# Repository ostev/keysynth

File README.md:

# KeySynth

KeySynth is an equation synthesiser built around a traditional mechanical keyboard!

An equation synthesiser is a wavetable synthesiser that allows the user to input arbitrary mathematical expressions which can then be used to create sounds! It also features a basic low-pass filter, with more effects (hopefully) to come.

In addition, it can act as a regular computer keyboard.

This repository contains the open-source PCBs (missing non-open source components from UltraLibrarian and SnapMagic) as well as project's source code. The PCB contains an 80% keyboard, three knobs, a pinout for a display, an ESP32-S3 (used for audio, display and USB) and an RP2040 (used for interfacing with the keyboard matrix due to limited pin availability).

The source code is divided into the following crates:

- [`calc`](crates/calc/) for the tiny programming language used for synthesis,
- [`repl`](crates/repl/) for a simple REPL for `calc` which is used for debugging and implementing new langauge features,
- [`synth`](crates/synth/) for the audio engine,
- [`keyboard_protocol`](crates/keyboard_protocol/) for interfacing between the RP2040 and the ESP32-S3 about keyboards and two of the three knobs over UART serial,
- [`keyboard_rp2040`](crates/keyboard_rp2040/) for running the keyboard matrix on the RP2040, and
- [`app`](crates/app/) for running the main application on the ESP32-S3.

## Demo

There'll be a link to a video demo up on YouTube once I've filmed it.

## :construction: :construction: :construction: Roadmap

This project isn't finished! Equation synthesis and keyboard input all work, but I want to implement some more features before considering it complete:

- [ ] USB MIDI input from host
- [ ] Improve PCB layout (as-is there are a couple of design flaws that don't inhabit the current set of functionality but limit the utility of 3.5mm audio output. I'm not sure when I'll be able to fix this: it'll be when I've made enough changes that I can justify the cost of ordering another set of PCBs.)
- [ ] Add more audio effects, like reverb and chorus.
- [ ] Add more audio synthesis engines, like subtractive or FM synthesis.

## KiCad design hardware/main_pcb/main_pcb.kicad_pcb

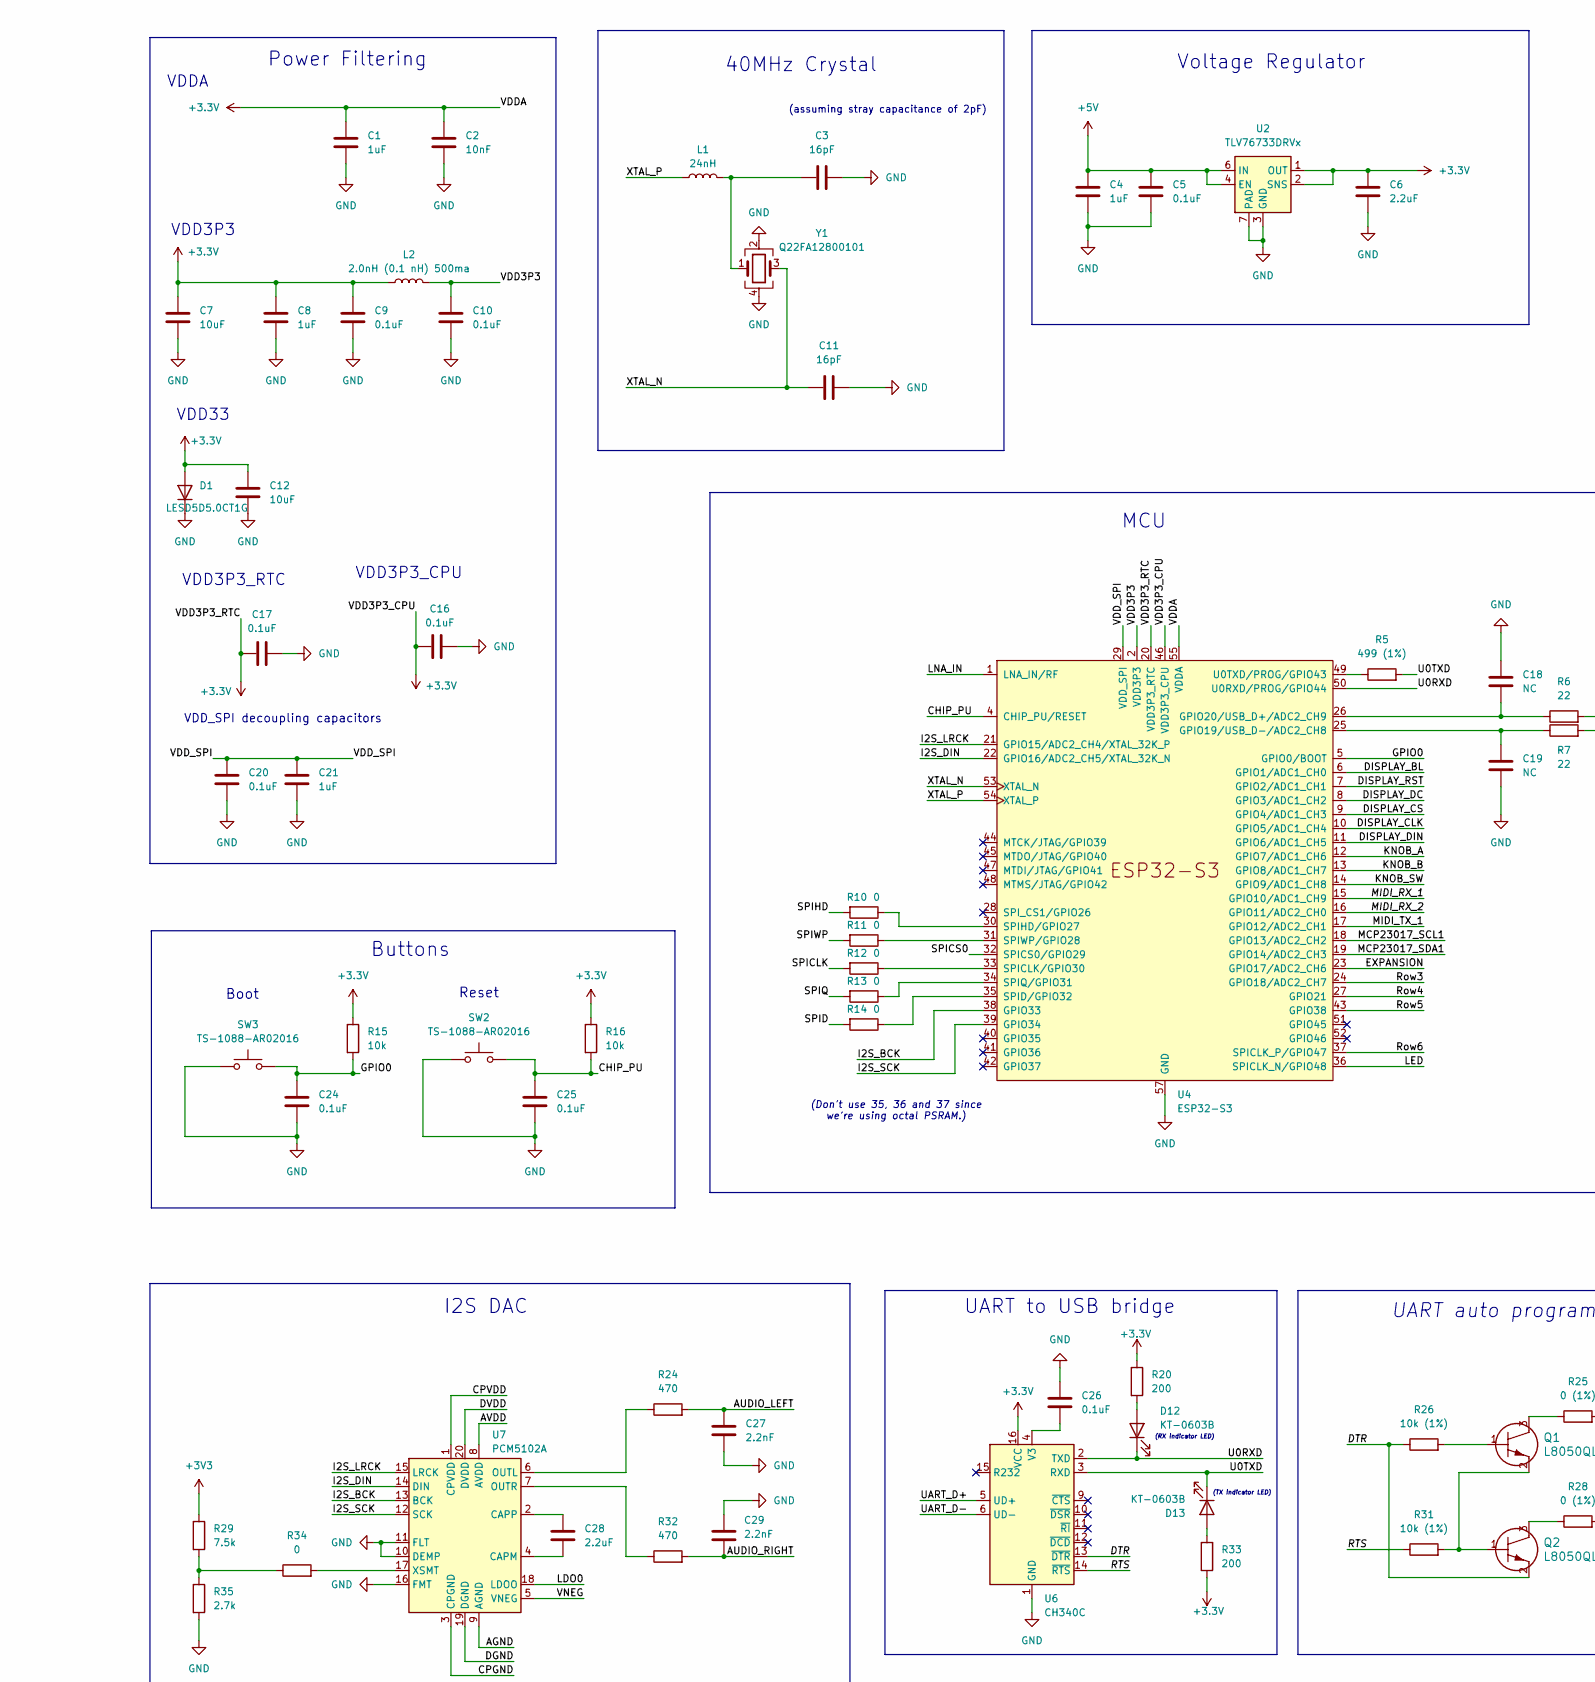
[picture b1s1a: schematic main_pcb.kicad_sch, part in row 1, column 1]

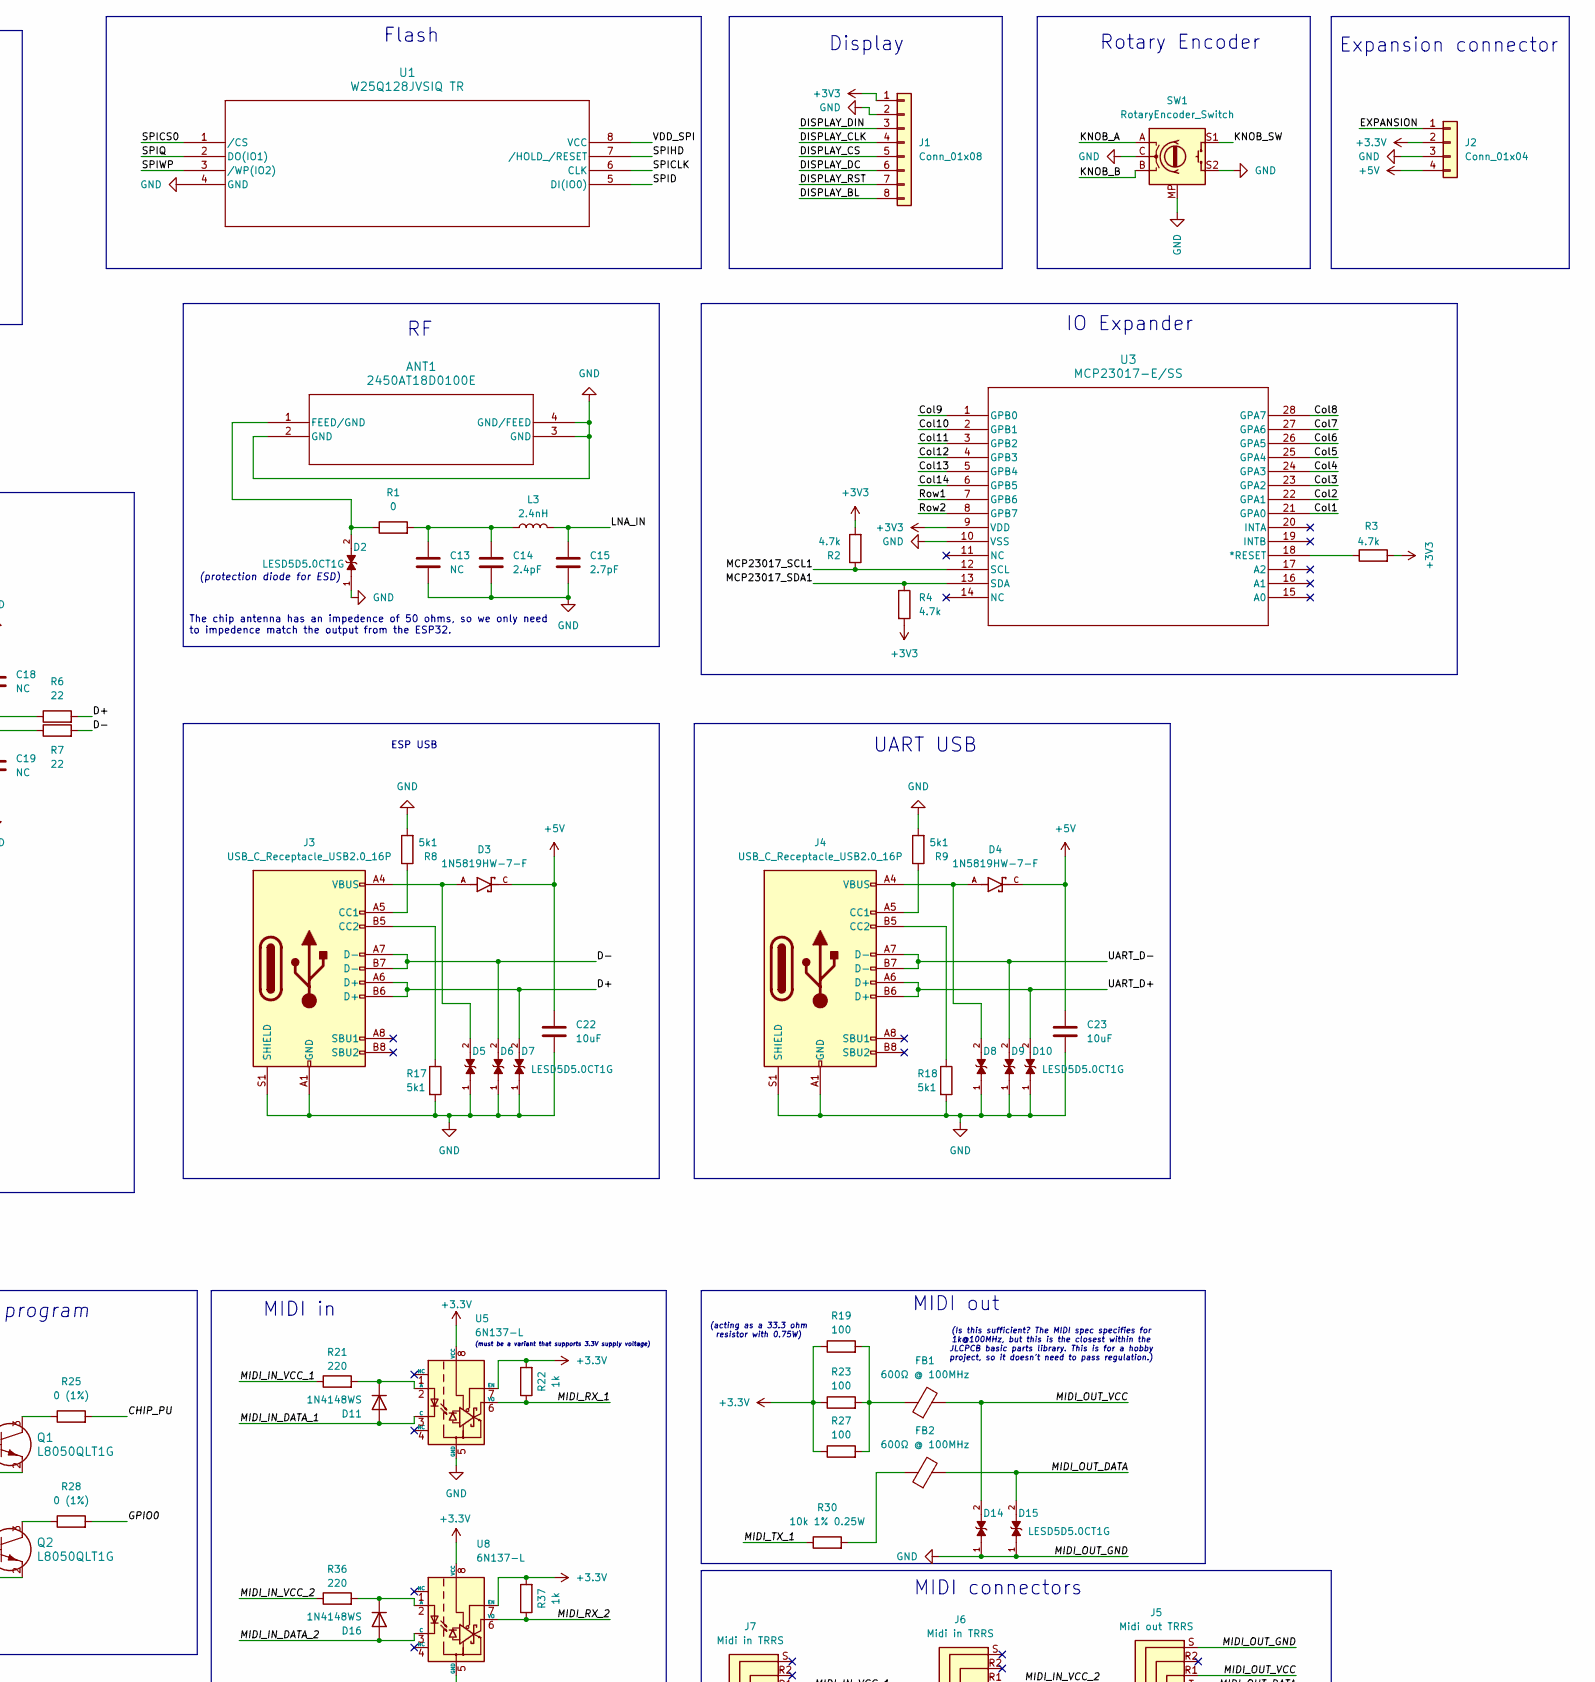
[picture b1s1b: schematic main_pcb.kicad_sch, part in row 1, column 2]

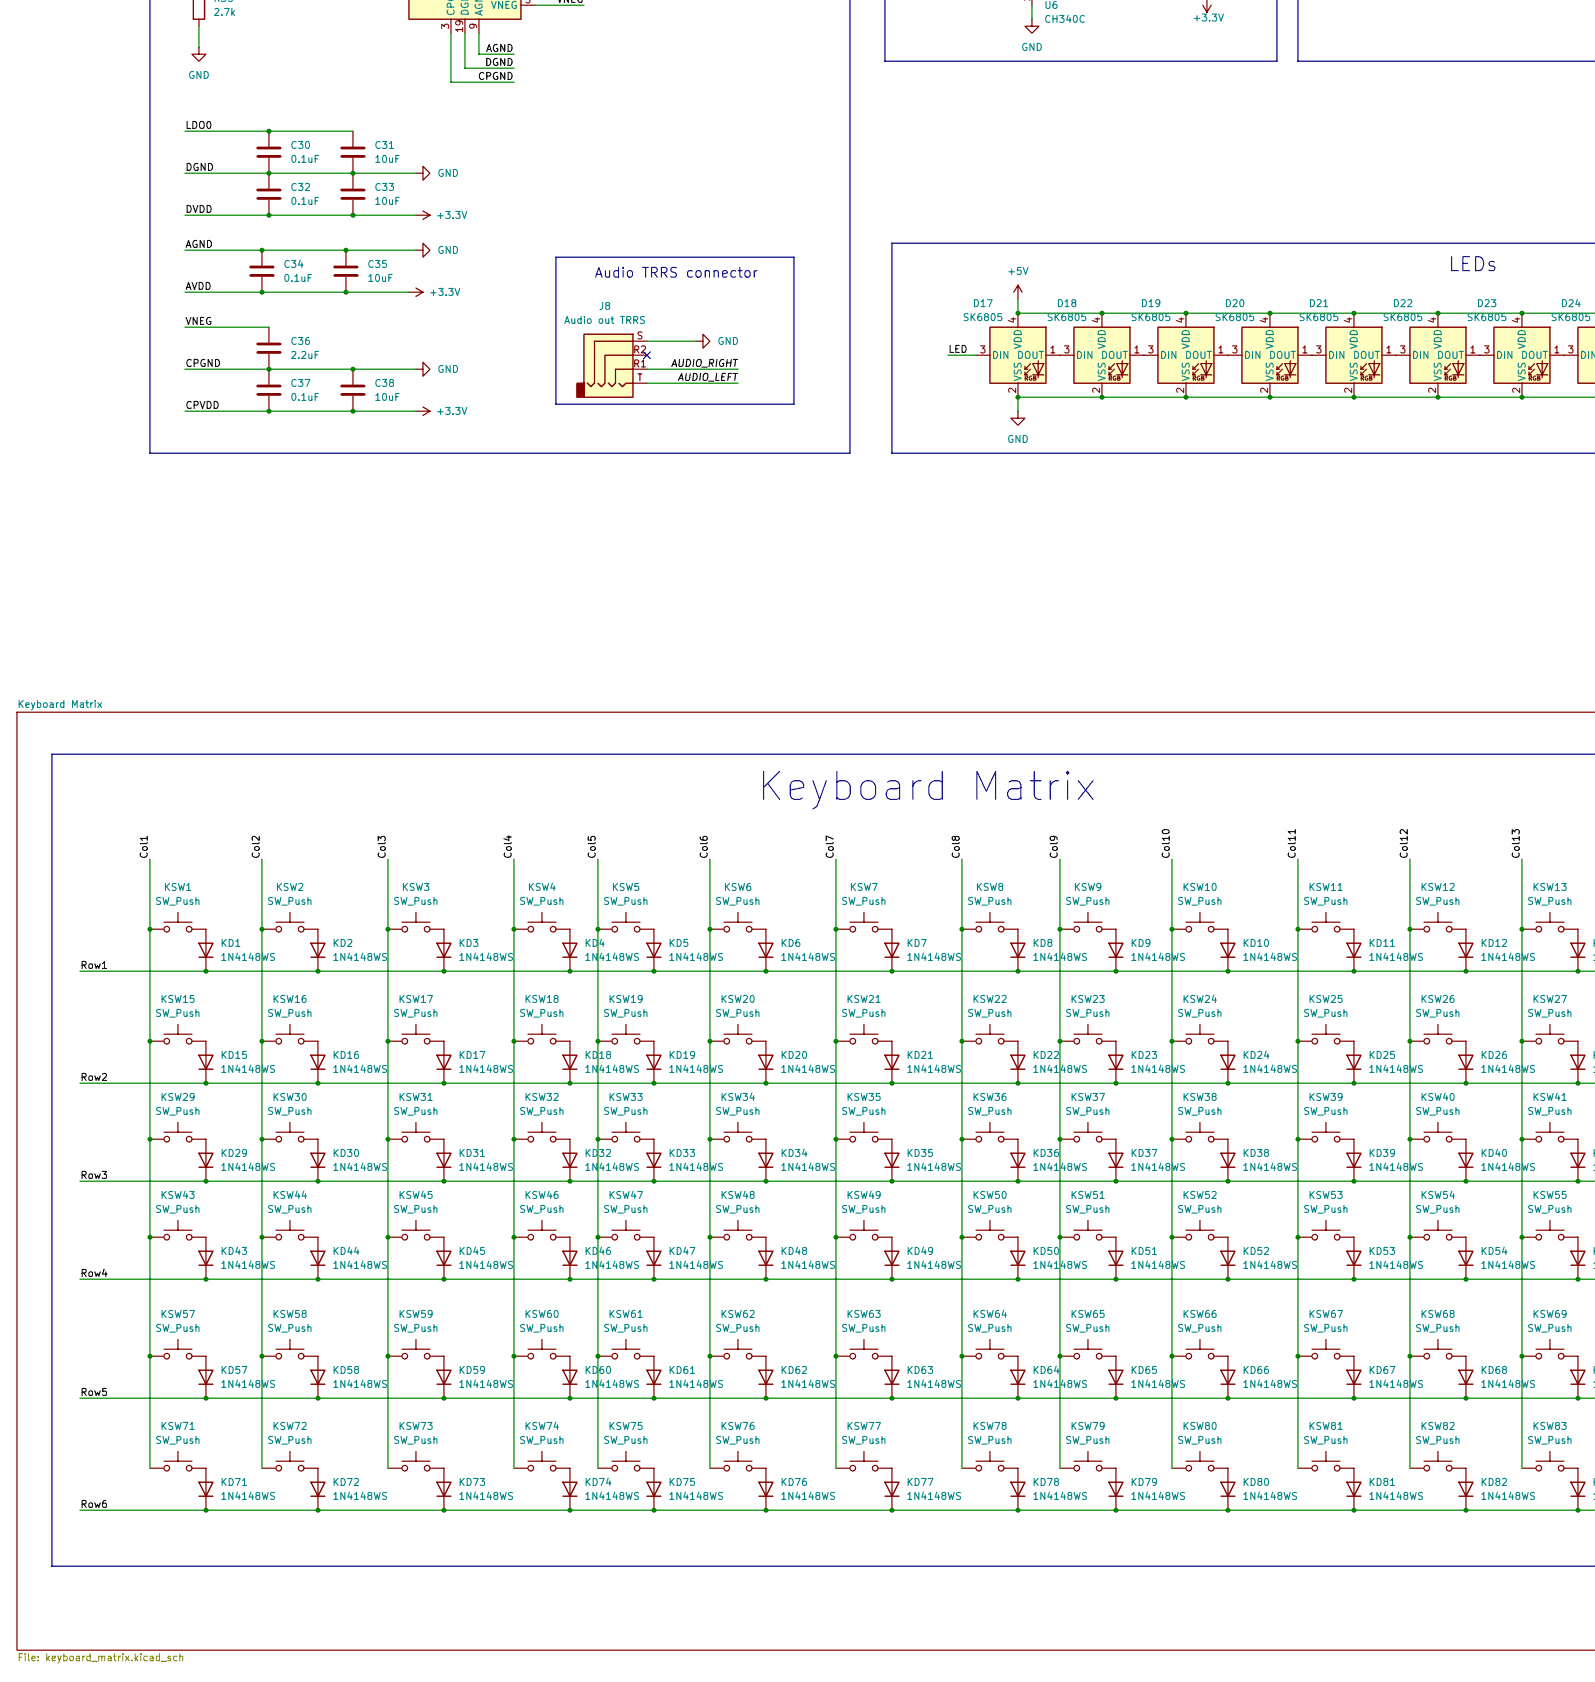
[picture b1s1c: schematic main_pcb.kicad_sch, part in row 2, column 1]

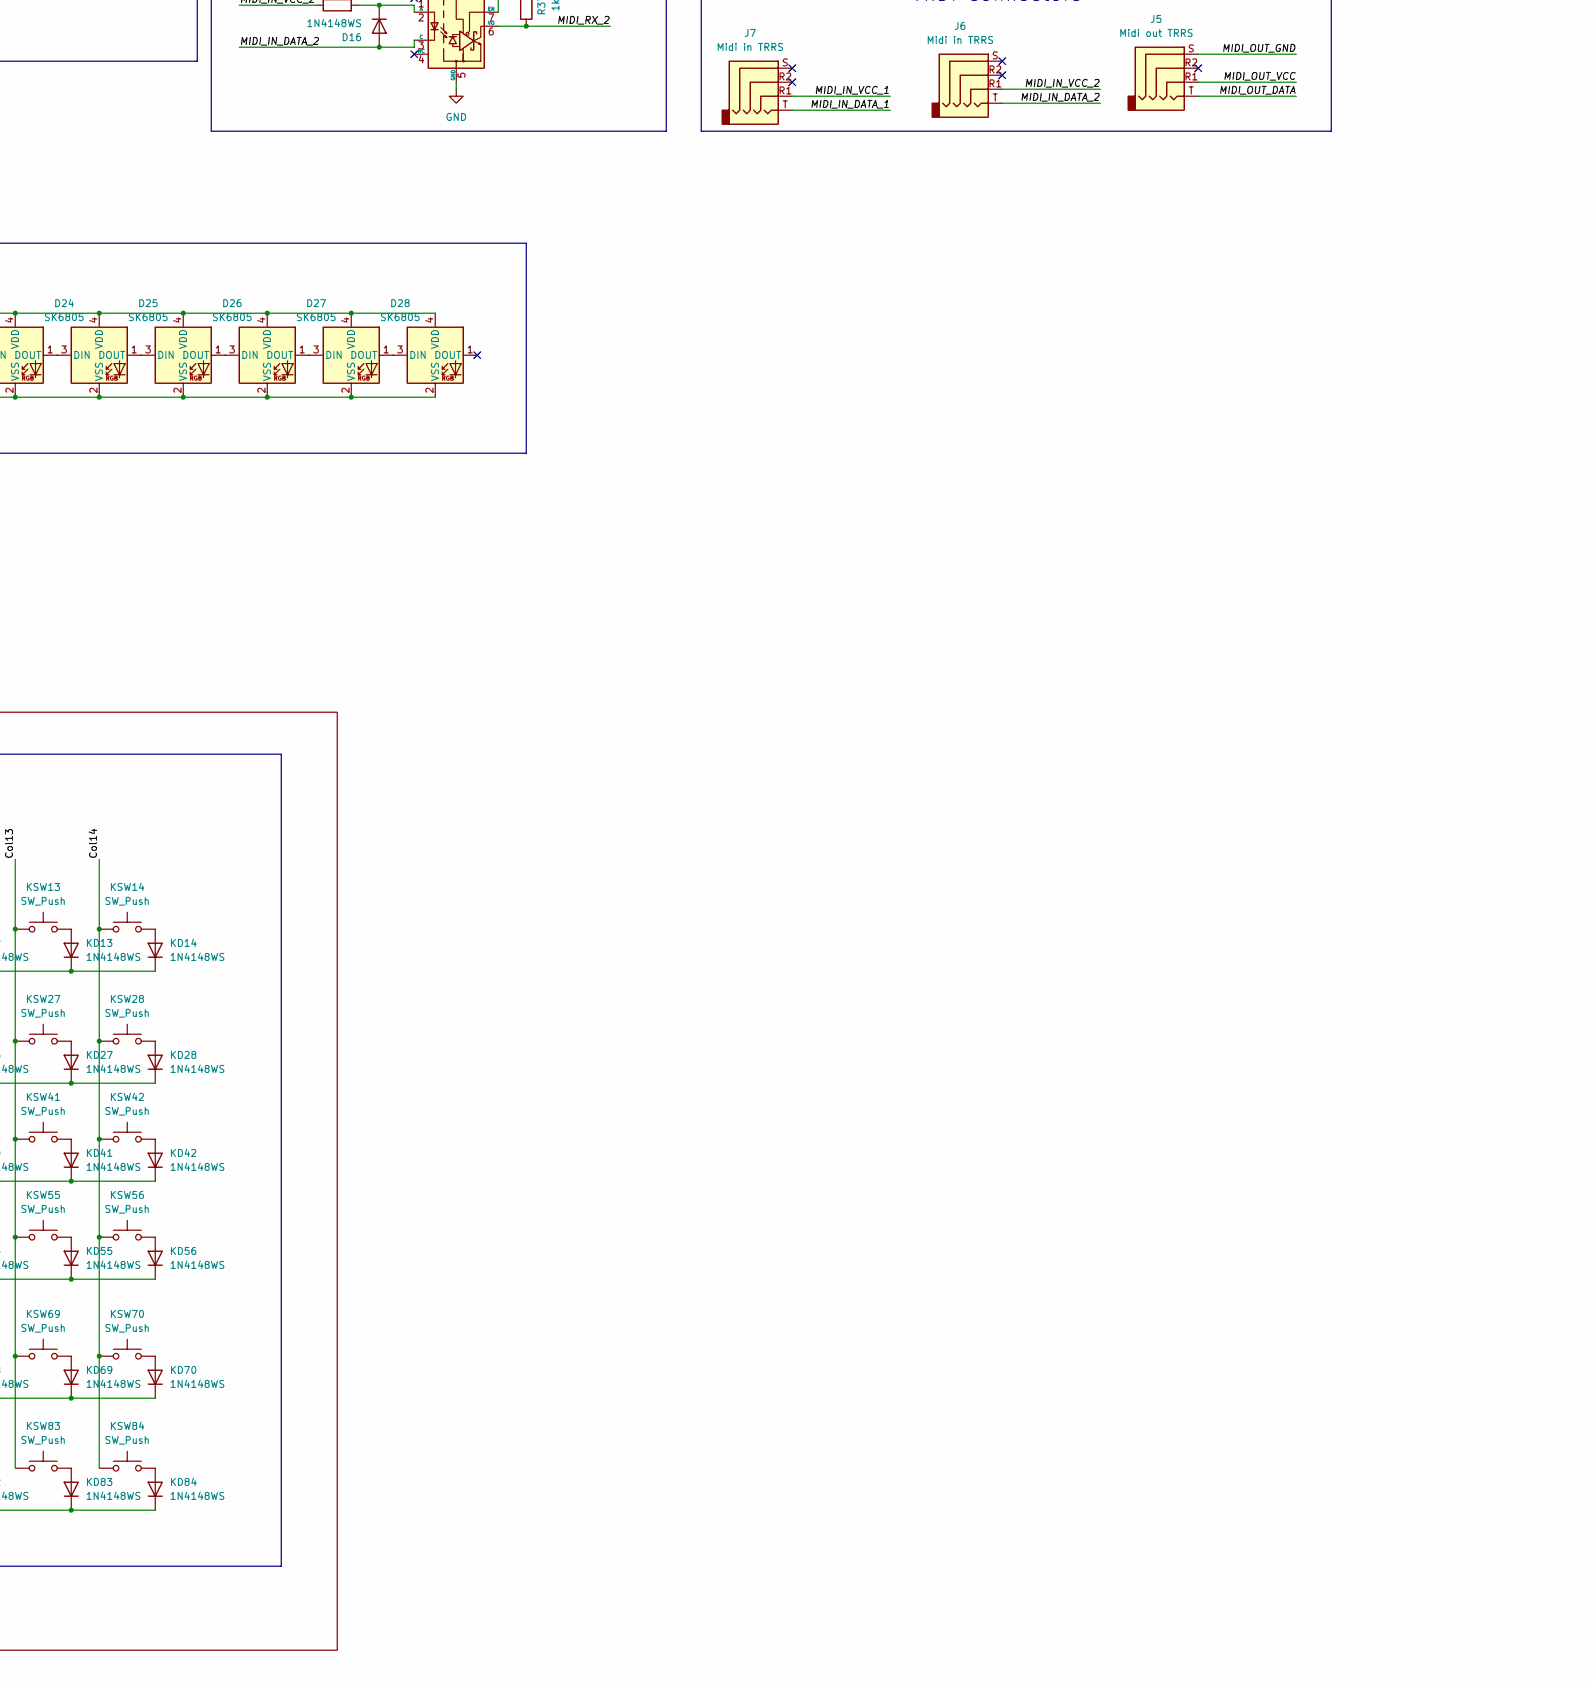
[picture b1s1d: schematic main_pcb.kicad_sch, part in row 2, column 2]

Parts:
ANT1: 2450AT18D0100E; 2450AT18D0100E_JOT
C1, C8, C21: 1uF; C_0603_1608Metric
C2: 10nF; C_0402_1005Metric
C3, C11: 16pF; C_0603_1608Metric
C4: 1uF; C_0402_1005Metric
C5, C10, C24, C25, C26, C30, C32, C34, C37: 0.1uF; C_0402_1005Metric
C6: 2.2uF; C_0402_1005Metric
C7, C12, C22, C23: 10uF; C_0603_1608Metric
C9, C16, C17, C20: 0.1uF; C_0603_1608Metric
C13, C18, C19: NC; C_0805_2012Metric_Pad1.18x1.45mm_HandSolder
C14: 2.4pF; C_0603_1608Metric
C15: 2.7pF; C_0603_1608Metric
C27, C29: 2.2nF; C_0603_1608Metric
C28, C36: 2.2uF; C_0603_1608Metric
C31, C33, C35, C38: 10uF; C_0402_1005Metric
D1: LESD5D5.0CT1G; TVS_LESD5D5.0CT1G
D2, D5, D6, D7, D8, D9, D10, D14, D15: LESD5D5.0CT1G; TVS_LESD5D5.0CT1G; PARTREV O
D3, D4: 1N5819HW-7-F; SOD3715X145N; PARTREV 18-2
D11, D16: 1N4148WS; D_SOD-323
D12, D13: KT-0603B; LED_0603_1608Metric
D17, D18, D19, D20, D21, D22, D23, D24, D25, D26, D27, D28: SK6805; LED_SK6805_PLCC4_2.4x2.7mm_P1.3mm
FB1, FB2: 600Ω @ 100MHz; L_0805_2012Metric
J1: Conn_01x08; PinHeader_1x08_P1.00mm_Vertical
J2: Conn_01x04; PinHeader_1x04_P2.54mm_Vertical
J3, J4: USB_C_Receptacle_USB2.0_16P; USB_C_Receptacle_HRO_TYPE-C-31-M-12; LCSC C165948
J5: Midi out TRRS; Jack_3.5mm_PJ320D_Horizontal
J6, J7: Midi in TRRS; Jack_3.5mm_PJ320D_Horizontal
J8: Audio out TRRS; Jack_3.5mm_PJ320D_Horizontal
KD1, KD2, KD3, KD4, KD5, KD6, KD7, KD8, KD9, KD10, KD11, KD12, KD13, KD14, KD15, KD16, KD17, KD18, KD19, KD20, KD21, KD22, KD23, KD24, KD25, KD26, KD27, KD28, KD29, KD30, KD31, KD32, KD33, KD34, KD35, KD36, KD37, KD38, KD39, KD40, KD41, KD42, KD43, KD44, KD45, KD46, KD47, KD48, KD49, KD50, KD51, KD52, KD53, KD54, KD55, KD56, KD57, KD58, KD59, KD60, KD61, KD62, KD63, KD64, KD65, KD66, KD67, KD68, KD69, KD70, KD71, KD72, KD73, KD74, KD75, KD76, KD77, KD78, KD79, KD80, KD81, KD82, KD83, KD84: 1N4148WS; D_SOD-323; LCSC C2128
KSW1, KSW2, KSW3, KSW4, KSW5, KSW6, KSW7, KSW8, KSW9, KSW10, KSW11, KSW12, KSW13, KSW14, KSW15, KSW16, KSW17, KSW18, KSW19, KSW20, KSW21, KSW22, KSW23, KSW24, KSW25, KSW26, KSW27, KSW28, KSW29, KSW30, KSW31, KSW32, KSW33, KSW34, KSW35, KSW36, KSW37, KSW38, KSW39, KSW40, KSW41, KSW42, KSW43, KSW44, KSW45, KSW46, KSW47, KSW48, KSW49, KSW50, KSW51, KSW52, KSW53, KSW54, KSW55, KSW56, KSW57, KSW58, KSW59, KSW60, KSW61, KSW62, KSW63, KSW64, KSW65, KSW66, KSW67, KSW68, KSW69, KSW70, KSW71, KSW72, KSW73, KSW74, KSW75, KSW76, KSW77, KSW78, KSW79, KSW80, KSW81, KSW82, KSW83, KSW84: SW_Push; SW_Cherry_MX_PCB_1.00u
L1: 24nH; L_0805_2012Metric
L2: 2.0nH (0.1 nH) 500ma; L_0402_1005Metric
L3: 2.4nH; L_0201_0603Metric
Q1, Q2: L8050QLT1G; SOT-23_LRC
R1: 0; R_0402_1005Metric
R2, R3, R4: 4.7k; R_0402_1005Metric
R5: 499 (1%); R_0402_1005Metric
R6, R7: 22; R_0402_1005Metric
R8, R9: 5k1; R_0402_1005Metric; LCSC C2021
R10, R11, R12, R13, R14, R34: 0; R_1206_3216Metric
R15, R16: 10k; R_0603_1608Metric
R17, R18: 5k1; R_0402_1005Metric
R19, R23, R27: 100; R_1206_3216Metric
R20, R33: 200; R_0402_1005Metric
R21, R36: 220; R_0603_1608Metric
R22, R37: 1k; R_0603_1608Metric
R24, R32: 470; R_0805_2012Metric
R25, R28: 0 (1%); R_1206_3216Metric
R26, R31: 10k (1%); R_0402_1005Metric
R29: 7.5k; R_0603_1608Metric
R30: 10k 1% 0.25W; R_1206_3216Metric
R35: 2.7k; R_0603_1608Metric
SW1: RotaryEncoder_Switch; RotaryEncoder_Alps_EC12E-Switch_Vertical_H20mm
SW2, SW3: TS-1088-AR02016; SW_TS-1088-AR02016
U1: W25Q128JVSIQ TR; SOIC_208MIL_WIN
U2: TLV76733DRVx; WSON-6-1EP_2x2mm_P0.65mm_EP1x1.6mm_ThermalVias
U3: MCP23017-E/SS; SSOP28_MC_MCH
U4: ESP32-S3; QFN-56-1EP_7x7mm_P0.4mm_EP5.6x5.6mm
U5, U8: 6N137-L; DIP-8_W7.62mm
U6: CH340C; SOIC-16_3.9x9.9mm_P1.27mm
U7: PCM5102A; TSSOP-20_4.4x6.5mm_P0.65mm
Y1: Q22FA12800101; Crystal_SMD_2016-4Pin_2.0x1.6mm

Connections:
+3.3V: C1.1, C2.1, C6.1, C7.1, C8.1, C9.1, C12.1, C16.1, C17.1, C32.2, C33.2, C34.2, C35.2, C37.2, C38.2, D1.2 (A), J2.2, L2.1, R15.1, R16.1, R19.1, R20.1, R22.2, R23.1, R27.1, R33.1, R37.2, U2.1 (OUT), U2.2 (SNS), U4.20 (VDD3P3_RTC), U4.46 (VDD3P3_CPU), U4.55 (VDDA), U4.56 (VDDA), U5.7 (EN), U5.8 (VCC), U6.16 (VCC), U7.1 (CPVDD), U7.8 (AVDD), U7.20 (DVDD), U8.7 (EN), U8.8 (VCC)
+3V3: J1.1, R2.2, R3.2, R4.2, R29.1, U3.9 (VDD)
+5V: C4.1, C5.1, C22.1, C23.1, D3.C, D4.C, D17.4 (VDD), D18.4 (VDD), D19.4 (VDD), D20.4 (VDD), D21.4 (VDD), D22.4 (VDD), D23.4 (VDD), D24.4 (VDD), D25.4 (VDD), D26.4 (VDD), D27.4 (VDD), D28.4 (VDD), J2.4, U2.4 (EN), U2.6 (IN)
/AUDIO_LEFT: C27.1, J8.T, R24.2
/AUDIO_RIGHT: C29.2, J8.R1, R32.2
/CHIP_PU: C25.1, R16.2, R25.2, SW2.2, U4.4 (CHIP_PU/RESET)
/Col1: KSW1.1, KSW15.1, KSW29.1, KSW43.1, KSW57.1, KSW71.1, U3.21 (GPA0)
/Col2: KSW2.1, KSW16.1, KSW30.1, KSW44.1, KSW58.1, KSW72.1, U3.22 (GPA1)
/Col3: KSW3.1, KSW17.1, KSW31.1, KSW45.1, KSW59.1, KSW73.1, U3.23 (GPA2)
/Col4: KSW4.1, KSW18.1, KSW32.1, KSW46.1, KSW60.1, KSW74.1, U3.24 (GPA3)
/Col5: KSW5.1, KSW19.1, KSW33.1, KSW47.1, KSW61.1, KSW75.1, U3.25 (GPA4)
/Col6: KSW6.1, KSW20.1, KSW34.1, KSW48.1, KSW62.1, KSW76.1, U3.26 (GPA5)
/Col7: KSW7.1, KSW21.1, KSW35.1, KSW49.1, KSW63.1, KSW77.1, U3.27 (GPA6)
/Col8: KSW8.1, KSW22.1, KSW36.1, KSW50.1, KSW64.1, KSW78.1, U3.28 (GPA7)
/Col9: KSW9.1, KSW23.1, KSW37.1, KSW51.1, KSW65.1, KSW79.1, U3.1 (GPB0)
/Col10: KSW10.1, KSW24.1, KSW38.1, KSW52.1, KSW66.1, KSW80.1, U3.2 (GPB1)
/Col11: KSW11.1, KSW25.1, KSW39.1, KSW53.1, KSW67.1, KSW81.1, U3.3 (GPB2)
/Col12: KSW12.1, KSW26.1, KSW40.1, KSW54.1, KSW68.1, KSW82.1, U3.4 (GPB3)
/Col13: KSW13.1, KSW27.1, KSW41.1, KSW55.1, KSW69.1, KSW83.1, U3.5 (GPB4)
/Col14: KSW14.1, KSW28.1, KSW42.1, KSW56.1, KSW70.1, KSW84.1, U3.6 (GPB5)
/D+: D7.2, J3.A6 (D+), J3.B6 (D+), R6.2
/D-: D6.2, J3.A7 (D-), J3.B7 (D-), R7.2
/DISPLAY_BL: J1.8, U4.6 (GPIO1/ADC1_CH0)
/DISPLAY_CLK: J1.4, U4.10 (GPIO5/ADC1_CH4)
/DISPLAY_CS: J1.5, U4.9 (GPIO4/ADC1_CH3)
/DISPLAY_DC: J1.6, U4.8 (GPIO3/ADC1_CH2)
/DISPLAY_DIN: J1.3, U4.11 (GPIO6/ADC1_CH5)
/DISPLAY_RST: J1.7, U4.7 (GPIO2/ADC1_CH1)
/DTR: Q2.2, R26.1, U6.13 (~DTR)
/EXPANSION: J2.1, U4.23 (GPIO17/ADC2_CH6)
/GPIO0: C24.1, R15.2, R28.2, SW3.2, U4.5 (GPIO0/BOOT)
/I2S_BCK: U4.38 (GPIO33), U7.13 (BCK)
/I2S_DIN: U4.22 (GPIO16/ADC2_CH5/XTAL_32K_N), U7.14 (DIN)
/I2S_LRCK: U4.21 (GPIO15/ADC2_CH4/XTAL_32K_P), U7.15 (LRCK)
/I2S_SCK: U4.39 (GPIO34), U7.12 (SCK)
/KNOB_A: SW1.A, U4.12 (GPIO7/ADC1_CH6)
/KNOB_B: SW1.B, U4.13 (GPIO8/ADC1_CH7)
/KNOB_SW: SW1.S1, U4.14 (GPIO9/ADC1_CH8)
/LDO0: C30.1, C31.1, U7.18 (LDOO)
/LED: D17.3 (DIN), U4.36 (SPICLK_N/GPIO48)
/LNA_IN: C15.1, L3.2, U4.1 (LNA_IN/RF)
/MCP23017_SCL1: R2.1, U3.12 (SCL), U4.18 (GPIO13/ADC2_CH2)
/MCP23017_SDA1: R4.1, U3.13 (SDA), U4.19 (GPIO14/ADC2_CH3)
/MIDI_IN_DATA_1: D11.2 (A), J7.T, U5.3 (C)
/MIDI_IN_DATA_2: D16.2 (A), J6.T, U8.3 (C)
/MIDI_IN_VCC_1: J7.R1, R21.1
/MIDI_IN_VCC_2: J6.R1, R36.1
/MIDI_OUT_DATA: D15.2, FB2.2, J5.T
/MIDI_OUT_VCC: D14.2, FB1.2, J5.R1
/MIDI_RX_1: R22.1, U4.15 (GPIO10/ADC1_CH9), U5.6 (VO)
/MIDI_RX_2: R37.1, U4.16 (GPIO11/ADC2_CH0), U8.6 (VO)
/MIDI_TX_1: R30.1, U4.17 (GPIO12/ADC2_CH1)
/RTS: R31.1, U6.14 (~RTS)
/Row1: KD1.1 (K), KD2.1 (K), KD3.1 (K), KD4.1 (K), KD5.1 (K), KD6.1 (K), KD7.1 (K), KD8.1 (K), KD9.1 (K), KD10.1 (K), KD11.1 (K), KD12.1 (K), KD13.1 (K), KD14.1 (K), U3.7 (GPB6)
/Row2: KD15.1 (K), KD16.1 (K), KD17.1 (K), KD18.1 (K), KD19.1 (K), KD20.1 (K), KD21.1 (K), KD22.1 (K), KD23.1 (K), KD24.1 (K), KD25.1 (K), KD26.1 (K), KD27.1 (K), KD28.1 (K), U3.8 (GPB7)
/Row3: KD29.1 (K), KD30.1 (K), KD31.1 (K), KD32.1 (K), KD33.1 (K), KD34.1 (K), KD35.1 (K), KD36.1 (K), KD37.1 (K), KD38.1 (K), KD39.1 (K), KD40.1 (K), KD41.1 (K), KD42.1 (K), U4.24 (GPIO18/ADC2_CH7)
/Row4: KD43.1 (K), KD44.1 (K), KD45.1 (K), KD46.1 (K), KD47.1 (K), KD48.1 (K), KD49.1 (K), KD50.1 (K), KD51.1 (K), KD52.1 (K), KD53.1 (K), KD54.1 (K), KD55.1 (K), KD56.1 (K), U4.27 (GPIO21)
/Row5: KD57.1 (K), KD58.1 (K), KD59.1 (K), KD60.1 (K), KD61.1 (K), KD62.1 (K), KD63.1 (K), KD64.1 (K), KD65.1 (K), KD66.1 (K), KD67.1 (K), KD68.1 (K), KD69.1 (K), KD70.1 (K), U4.43 (GPIO38)
/Row6: KD71.1 (K), KD72.1 (K), KD73.1 (K), KD74.1 (K), KD75.1 (K), KD76.1 (K), KD77.1 (K), KD78.1 (K), KD79.1 (K), KD80.1 (K), KD81.1 (K), KD82.1 (K), KD83.1 (K), KD84.1 (K), U4.37 (SPICLK_P/GPIO47)
/SPICLK: R12.2, U1.6 (CLK)
/SPICS0: U1.1 (/CS), U4.32 (SPICS0/GPIO29)
/SPID: R14.2, U1.5 (DI(IO0))
/SPIHD: R10.2, U1.7 (/HOLD_/RESET)
/SPIQ: R13.2, U1.2 (DO(IO1))
/SPIWP: R11.2, U1.3 (/WP(IO2))
/U0RXD: D12.1 (K), U4.50 (U0RXD/PROG/GPIO44), U6.2 (TXD)
/U0TXD: D13.1 (K), R5.2, U6.3 (RXD)
/UART_D+: D10.2, J4.A6 (D+), J4.B6 (D+), U6.5 (UD+)
/UART_D-: D9.2, J4.A7 (D-), J4.B7 (D-), U6.6 (UD-)
/VDD_SPI: C20.1, C21.1, U1.8 (VCC), U4.29 (VDD_SPI)
/VNEG: C36.1, U7.5 (VNEG)
/XTAL_N: C11.2, U4.53 (XTAL_N), Y1.3
/XTAL_P: L1.1, U4.54 (XTAL_P)
GND: ANT1.2 (GND), ANT1.3 (GND), ANT1.4 (GND/FEED), C1.2, C2.2, C3.1, C4.2, C5.2, C6.2, C7.2, C8.2, C9.2, C10.2, C11.1, C12.2, C13.2, C14.2, C15.2, C16.2, C17.2, C18.1, C19.2, C20.2, C21.2, C22.2, C23.2, C24.2, C25.2, C26.1, C27.2, C29.1, C30.2, C31.2, C32.1, C33.1, C34.1, C35.1, C36.2, C37.1, C38.1, D1.1 (K), D2.1, D5.1, D6.1, D7.1, D8.1, D9.1, D10.1, D14.1, D15.1, D17.2 (VSS), D18.2 (VSS), D19.2 (VSS), D20.2 (VSS), D21.2 (VSS), D22.2 (VSS), D23.2 (VSS), D24.2 (VSS), D25.2 (VSS), D26.2 (VSS), D27.2 (VSS), D28.2 (VSS), J1.2, J2.3, J3.A1 (GND), J3.A12 (GND), J3.B1 (GND), J3.B12 (GND), J3.S1 (SHIELD), J4.A1 (GND), J4.A12 (GND), J4.B1 (GND), J4.B12 (GND), J4.S1 (SHIELD), J5.S, J8.S, R8.2, R9.2, R17.2, R18.2, R35.2, SW1.C, SW1.MP, SW1.S2, SW2.1, SW3.1, U1.4 (GND), U2.3 (GND), U2.5 (GND), U2.7 (PAD), U3.10 (VSS), U4.57 (GND), U5.5 (GND), U6.1 (GND), U7.3 (CPGND), U7.9 (AGND), U7.10 (DEMP), U7.11 (FLT), U7.16 (FMT), U7.19 (DGND), U8.5 (GND), Y1.2, Y1.4
unnamed: ANT1.1 (FEED/GND), D2.2, R1.1
unnamed: C3.2, L1.2, Y1.1
unnamed: C13.1, C14.1, L3.1, R1.2
unnamed: D3.A, D5.2, J3.A4 (VBUS), J3.A9 (VBUS), J3.B4 (VBUS), J3.B9 (VBUS)
unnamed: D4.A, D8.2, J4.A4 (VBUS), J4.A9 (VBUS), J4.B4 (VBUS), J4.B9 (VBUS)
unnamed: D11.1 (K), R21.2, U5.2 (A)
unnamed: D12.2 (A), R20.2
unnamed: D13.2 (A), R33.2
unnamed: D16.1 (K), R36.2, U8.2 (A)
unnamed: D17.1 (DOUT), D18.3 (DIN)
unnamed: D18.1 (DOUT), D19.3 (DIN)
unnamed: D19.1 (DOUT), D20.3 (DIN)
unnamed: D20.1 (DOUT), D21.3 (DIN)
unnamed: D21.1 (DOUT), D22.3 (DIN)
unnamed: D22.1 (DOUT), D23.3 (DIN)
unnamed: D23.1 (DOUT), D24.3 (DIN)
unnamed: D24.1 (DOUT), D25.3 (DIN)
unnamed: D25.1 (DOUT), D26.3 (DIN)
unnamed: D26.1 (DOUT), D27.3 (DIN)
unnamed: D27.1 (DOUT), D28.3 (DIN)
unnamed: FB1.1, R19.2, R23.2, R27.2
unnamed: FB2.1, R30.2
unnamed: J3.A5 (CC1), R8.1
unnamed: J3.B5 (CC2), R17.1
unnamed: J4.A5 (CC1), R9.1
unnamed: J4.B5 (CC2), R18.1
unnamed: KD1.2 (A), KSW1.2
unnamed: KD2.2 (A), KSW2.2
unnamed: KD3.2 (A), KSW3.2
unnamed: KD4.2 (A), KSW4.2
unnamed: KD5.2 (A), KSW5.2
unnamed: KD6.2 (A), KSW6.2
unnamed: KD7.2 (A), KSW7.2
unnamed: KD8.2 (A), KSW8.2
unnamed: KD9.2 (A), KSW9.2
unnamed: KD10.2 (A), KSW10.2
unnamed: KD11.2 (A), KSW11.2
unnamed: KD12.2 (A), KSW12.2
unnamed: KD13.2 (A), KSW13.2
unnamed: KD14.2 (A), KSW14.2
unnamed: KD15.2 (A), KSW15.2
unnamed: KD16.2 (A), KSW16.2
unnamed: KD17.2 (A), KSW17.2
unnamed: KD18.2 (A), KSW18.2
unnamed: KD19.2 (A), KSW19.2
unnamed: KD20.2 (A), KSW20.2
unnamed: KD21.2 (A), KSW21.2
unnamed: KD22.2 (A), KSW22.2
unnamed: KD23.2 (A), KSW23.2
unnamed: KD24.2 (A), KSW24.2
unnamed: KD25.2 (A), KSW25.2
unnamed: KD26.2 (A), KSW26.2
unnamed: KD27.2 (A), KSW27.2
unnamed: KD28.2 (A), KSW28.2
unnamed: KD29.2 (A), KSW29.2
unnamed: KD30.2 (A), KSW30.2
unnamed: KD31.2 (A), KSW31.2
unnamed: KD32.2 (A), KSW32.2
unnamed: KD33.2 (A), KSW33.2
unnamed: KD34.2 (A), KSW34.2
unnamed: KD35.2 (A), KSW35.2
unnamed: KD36.2 (A), KSW36.2
unnamed: KD37.2 (A), KSW37.2
unnamed: KD38.2 (A), KSW38.2
unnamed: KD39.2 (A), KSW39.2
unnamed: KD40.2 (A), KSW40.2
unnamed: KD41.2 (A), KSW41.2
unnamed: KD42.2 (A), KSW42.2
unnamed: KD43.2 (A), KSW43.2
unnamed: KD44.2 (A), KSW44.2
unnamed: KD45.2 (A), KSW45.2
unnamed: KD46.2 (A), KSW46.2
unnamed: KD47.2 (A), KSW47.2
unnamed: KD48.2 (A), KSW48.2
unnamed: KD49.2 (A), KSW49.2
unnamed: KD50.2 (A), KSW50.2
unnamed: KD51.2 (A), KSW51.2
unnamed: KD52.2 (A), KSW52.2
unnamed: KD53.2 (A), KSW53.2
unnamed: KD54.2 (A), KSW54.2
unnamed: KD55.2 (A), KSW55.2
unnamed: KD56.2 (A), KSW56.2
unnamed: KD57.2 (A), KSW57.2
unnamed: KD58.2 (A), KSW58.2
unnamed: KD59.2 (A), KSW59.2
unnamed: KD60.2 (A), KSW60.2
unnamed: KD61.2 (A), KSW61.2
unnamed: KD62.2 (A), KSW62.2
unnamed: KD63.2 (A), KSW63.2
unnamed: KD64.2 (A), KSW64.2
unnamed: KD65.2 (A), KSW65.2
unnamed: KD66.2 (A), KSW66.2
unnamed: KD67.2 (A), KSW67.2
unnamed: KD68.2 (A), KSW68.2
unnamed: KD69.2 (A), KSW69.2
unnamed: KD70.2 (A), KSW70.2
unnamed: KD71.2 (A), KSW71.2
unnamed: KD72.2 (A), KSW72.2
unnamed: KD73.2 (A), KSW73.2
unnamed: KD74.2 (A), KSW74.2
unnamed: KD75.2 (A), KSW75.2
unnamed: KD76.2 (A), KSW76.2
unnamed: KD77.2 (A), KSW77.2
unnamed: KD78.2 (A), KSW78.2
unnamed: KD79.2 (A), KSW79.2
unnamed: KD80.2 (A), KSW80.2
unnamed: KD81.2 (A), KSW81.2
unnamed: KD82.2 (A), KSW82.2
unnamed: KD83.2 (A), KSW83.2
unnamed: KD84.2 (A), KSW84.2
unnamed: Q1.1, R26.2
unnamed: Q1.2, Q2.1, R31.2
unnamed: Q1.3, R25.1
unnamed: Q2.3, R28.1
unnamed: R29.2, R34.1, R35.1
unnamed: R3.1, U3.18 (*RESET)
unnamed: C19.1, R7.1, U4.25 (GPIO19/USB_D-/ADC2_CH8)
unnamed: C18.2, R6.1, U4.26 (GPIO20/USB_D+/ADC2_CH9)
unnamed: R12.1, U4.33 (SPICLK/GPIO30)
unnamed: R14.1, U4.35 (SPID/GPIO32)
unnamed: R10.1, U4.30 (SPIHD/GPIO27)
unnamed: R13.1, U4.34 (SPIQ/GPIO31)
unnamed: R11.1, U4.31 (SPIWP/GPIO28)
unnamed: R5.1, U4.49 (U0TXD/PROG/GPIO43)
unnamed: C26.2, U6.4 (V3)
unnamed: C28.2, U7.4 (CAPM)
unnamed: C28.1, U7.2 (CAPP)
unnamed: R24.1, U7.6 (OUTL)
unnamed: R32.1, U7.7 (OUTR)
unnamed: R34.2, U7.17 (XSMT)
VDD3P3: C10.1, L2.2, U4.2 (VDD3P3), U4.3 (VDD3P3)

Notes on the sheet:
(protection diode for ESD)
The chip antenna has an impedence of 50 ohms, so we only need to impedence match the output from the ESP32.
Reset
UART USB
MIDI in
IO Expander
Display
MIDI out
(Is this sufficient? The MIDI spec specifies for 1k@100MHz, but this is the closest within the JLCPCB basic parts library. This is for a hobby project, so it doesn't need to pass regulation.)
Keyboard Matrix
UART auto program
Voltage Regulator
VDD3P3
Flash
(TX indicator LED)
(acting as a 33.3 ohm resistor with 0.75W)
Power Filtering
MCU
(Don't use 35, 36 and 37 since we're using octal PSRAM.)
VDD3P3_RTC
(assuming stray capacitance of 2pF)
ESP USB
VDD3P3_CPU
Boot
Audio TRRS connector
40MHz Crystal
LEDs
UART to USB bridge
Buttons
VDD33
I2S DAC
(RX indicator LED)
Rotary Encoder
VDD_SPI decoupling capacitors
(must be a variant that supports 3.3V supply voltage)
MIDI connectors
VDDA
Expansion connector

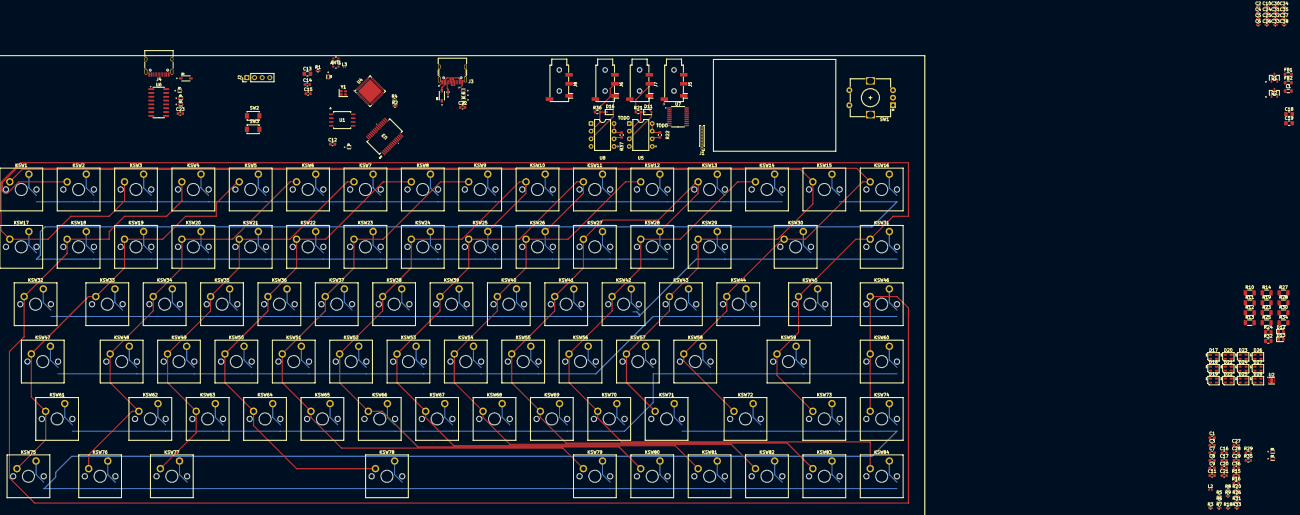
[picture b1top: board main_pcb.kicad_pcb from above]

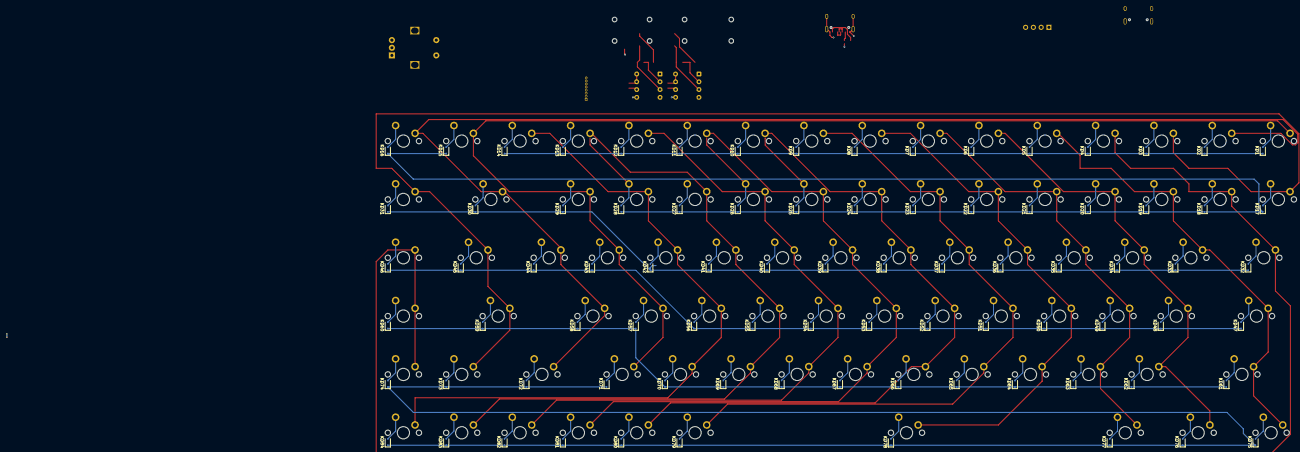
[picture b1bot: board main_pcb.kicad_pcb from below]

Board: 2 copper layers, 299 parts (84 on the bottom side), 205 nets.

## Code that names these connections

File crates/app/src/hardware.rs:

use esp_hal::{
    Blocking,
    clock::CpuClock,
    dma::{self, DmaRxBuf, DmaTxBuf},
    dma_buffers,
    gpio::{Level, Output, OutputConfig},
    interrupt::software::{SoftwareInterrupt, SoftwareInterruptControl},
    pcnt::Pcnt,
    peripherals::{CPU_CTRL, GPIO7, GPIO8},
    psram::{FlashFreq, SpiRamFreq},
    spi::{self, master::Spi},
    time::Rate,
    timer::timg::TimerGroup,
    uart::{self, UartRx},
};
use esp_println::println;
use esp_storage::FlashStorage;
use keyboard_protocol::uart::BAUDRATE;

use crate::{
    gui::display::{self, DisplayHardware},
    input::{encoder, keyboard::KeyboardHardware},
    storage::StorageHardware,
    usb,
};

/// Contains all the hardware that the synthesiser talks to.
pub struct Hardware {
    pub interrupt_1: SoftwareInterrupt<'static, 1>,
    pub interrupt_2: SoftwareInterrupt<'static, 2>,
    pub cpu_control: CPU_CTRL<'static>,

    pub keyboard: KeyboardHardware,
    pub encoder: encoder::Hardware<GPIO7<'static>, GPIO8<'static>>,

    pub display: DisplayHardware,

    pub usb: usb::UsbHardware,
    pub storage: StorageHardware,
}

/// An error that occurred during hardware initialisation.
#[derive(Debug)]
pub enum InitError {
    UartConfigError(uart::ConfigError),
    SpiConfigError(spi::master::ConfigError),
    DmaBufError(dma::DmaBufError),
}

impl Hardware {
    pub async fn new() -> Result<Hardware, InitError> {
        let peripherals = esp_hal::init(esp_hal::Config::default().with_cpu_clock(CpuClock::max()));

        // Initialise heap memory
        esp_alloc::psram_allocator!(
            peripherals.PSRAM,
            esp_hal::psram,
            esp_hal::psram::PsramConfig {
                mode: esp_hal::psram::PsramMode::OctalSpi,
                size: esp_hal::psram::PsramSize::AutoDetect,
                core_clock: None,
                flash_frequency: FlashFreq::FlashFreq80m,
                ram_frequency: SpiRamFreq::Freq80m,
            }
        );

        let software_interrupt = SoftwareInterruptControl::new(peripherals.SW_INTERRUPT);
        let timer_group_0 = TimerGroup::new(peripherals.TIMG0);

        // Start the executor
        esp_rtos::start(timer_group_0.timer0, software_interrupt.software_interrupt0);

        // This is used later to start the second core
        let cpu_control = peripherals.CPU_CTRL;

        // UART receiver from RP2040
        let keyboard = {
            let uart = UartRx::new(
                peripherals.UART1,
                uart::Config::default().with_baudrate(BAUDRATE),
            )
            .map_err(InitError::UartConfigError)?
            .with_rx(peripherals.GPIO12);

            KeyboardHardware { uart }
        };

        println!("Keyboard setup complete!");

        // The primary encoder hardware
        let encoder = {
            encoder::Hardware {
                counter: Pcnt::new(peripherals.PCNT),
                a: peripherals.GPIO7,
                b: peripherals.GPIO8,
            }
        };

        // The SPI display driver
        let display = {
            let (rx_buffer, rx_descriptors, tx_buffer, tx_descriptors) = dma_buffers!(32_000);

            let dma_rx_buf =
                DmaRxBuf::new(rx_descriptors, rx_buffer).map_err(InitError::DmaBufError)?;
            let dma_tx_buf =
                DmaTxBuf::new(tx_descriptors, tx_buffer).map_err(InitError::DmaBufError)?;

            let spi: esp_hal::spi::master::SpiDmaBus<'static, Blocking> = Spi::new(
                peripherals.SPI2,
                spi::master::Config::default()
                    .with_frequency(Rate::from_mhz(20))
                    .with_mode(spi::Mode::_0),
            )
            .map_err(InitError::SpiConfigError)?
            .with_sck(peripherals.GPIO2)
            .with_cs(peripherals.GPIO3)
            .with_mosi(peripherals.GPIO1)
            .with_dma(peripherals.DMA_CH1)
            .with_buffers(dma_rx_buf, dma_tx_buf);

            let dc_pin = Output::new(peripherals.GPIO4, Level::Low, OutputConfig::default());
            let reset_pin = Output::new(peripherals.GPIO5, Level::Low, OutputConfig::default());

            display::DisplayHardware {
                spi,
                reset_pin,
                dc_pin,
            }
        };

        println!("Display setup complete!");

        let storage = StorageHardware {
            flash: FlashStorage::new(peripherals.FLASH),
        };

        println!("Storage setup complete!");

        let usb = usb::Peripherals {
            usb: peripherals.USB0,
            dp: peripherals.GPIO20,
            dm: peripherals.GPIO19,
        }
        .build();

        println!("USB setup complete!");

        Ok(Hardware {
            interrupt_1: software_interrupt.software_interrupt1,
            interrupt_2: software_interrupt.software_interrupt2,
            cpu_control,

            keyboard,
            encoder,
            usb,
            display,
            storage,
        })
    }
}
